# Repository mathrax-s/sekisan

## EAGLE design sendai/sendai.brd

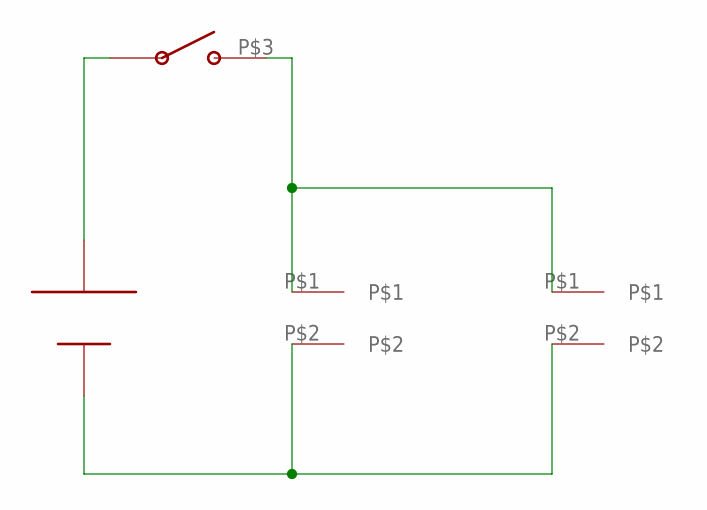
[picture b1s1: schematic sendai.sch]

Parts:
U$1: CR2032
U$2, U$3: CON2
U$4: LEAD_SWITCH

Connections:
unnamed: U$2.P$1, U$3.P$1, U$4.P$3
unnamed: U$1.-1 (-), U$2.P$2, U$3.P$2
unnamed: U$1.+1 (+), U$4.P$4

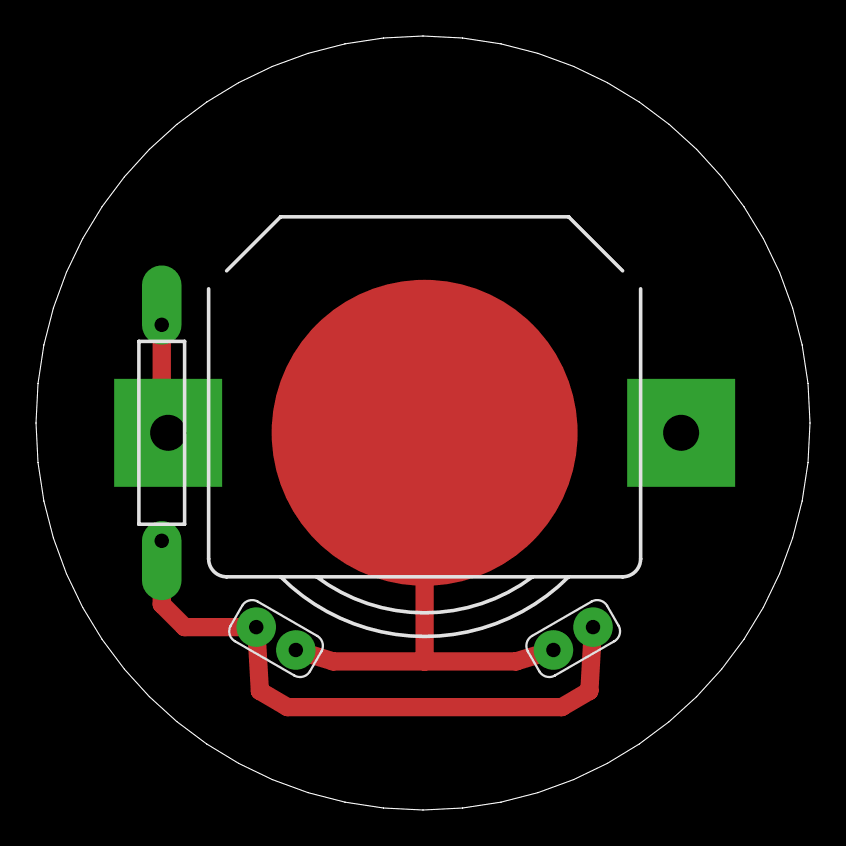
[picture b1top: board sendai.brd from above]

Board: 2 copper layers, 43.0 x 43.0 mm, 4 parts (0 on the bottom side), 3 nets.

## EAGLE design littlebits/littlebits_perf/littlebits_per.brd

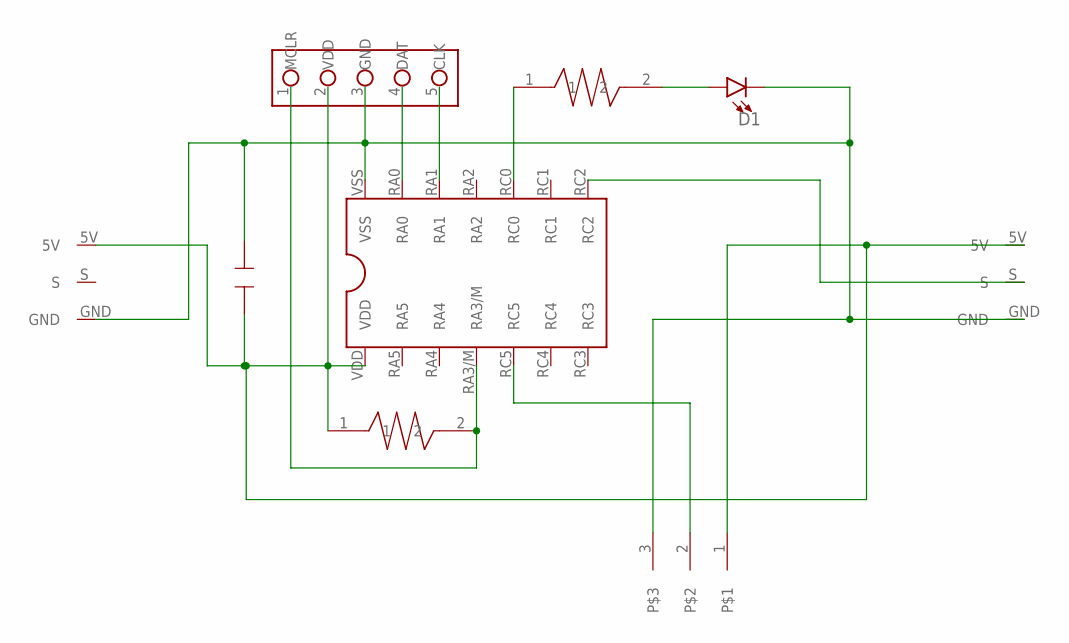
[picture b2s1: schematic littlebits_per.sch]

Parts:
D1: LED-3MM-NO_SILK; LED_3MM-NS
U$1: ICSP
U$2: 14PIN_DIP
U$3, U$8: RESISTOR
U$4: CAP-CERAMIC
U$5, U$6: LITTLEBITS_CON
U$7: CON3

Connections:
unnamed: U$2.RC5, U$7.2
unnamed: U$1.4 (DAT), U$2.RA0
unnamed: U$1.5 (CLK), U$2.RA1
unnamed: U$1.2 (VDD), U$2.VDD, U$3.1, U$4.1, U$5.5V, U$6.5V, U$7.1
unnamed: U$1.1 (MCLR), U$2.RA3/M, U$3.2
unnamed: U$2.RC0, U$8.1
unnamed: U$2.RC2, U$6.S
unnamed: D1.A, U$8.2
unnamed: D1.K (C), U$1.3 (GND), U$2.VSS, U$4.2, U$5.GND, U$6.GND, U$7.3

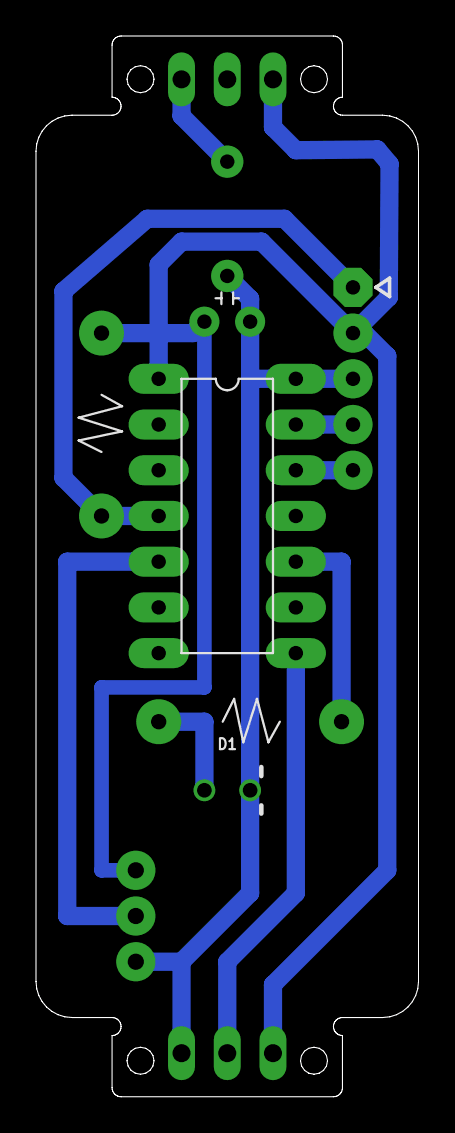
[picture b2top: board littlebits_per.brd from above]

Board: 2 copper layers, 21.2 x 58.9 mm, 9 parts (0 on the bottom side), 9 nets.

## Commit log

2018-06-21 first
2018-06-22 lead switch

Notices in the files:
parts and their libraries:
SparkFun-LED: Licensing: Creative Commons ShareAlike 4.0 International - https://creativecommons.org/licenses/by-sa/4.0
